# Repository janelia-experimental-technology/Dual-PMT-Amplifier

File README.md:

# Dual-PMT-Amplifier
Dual amplifier for PMTs

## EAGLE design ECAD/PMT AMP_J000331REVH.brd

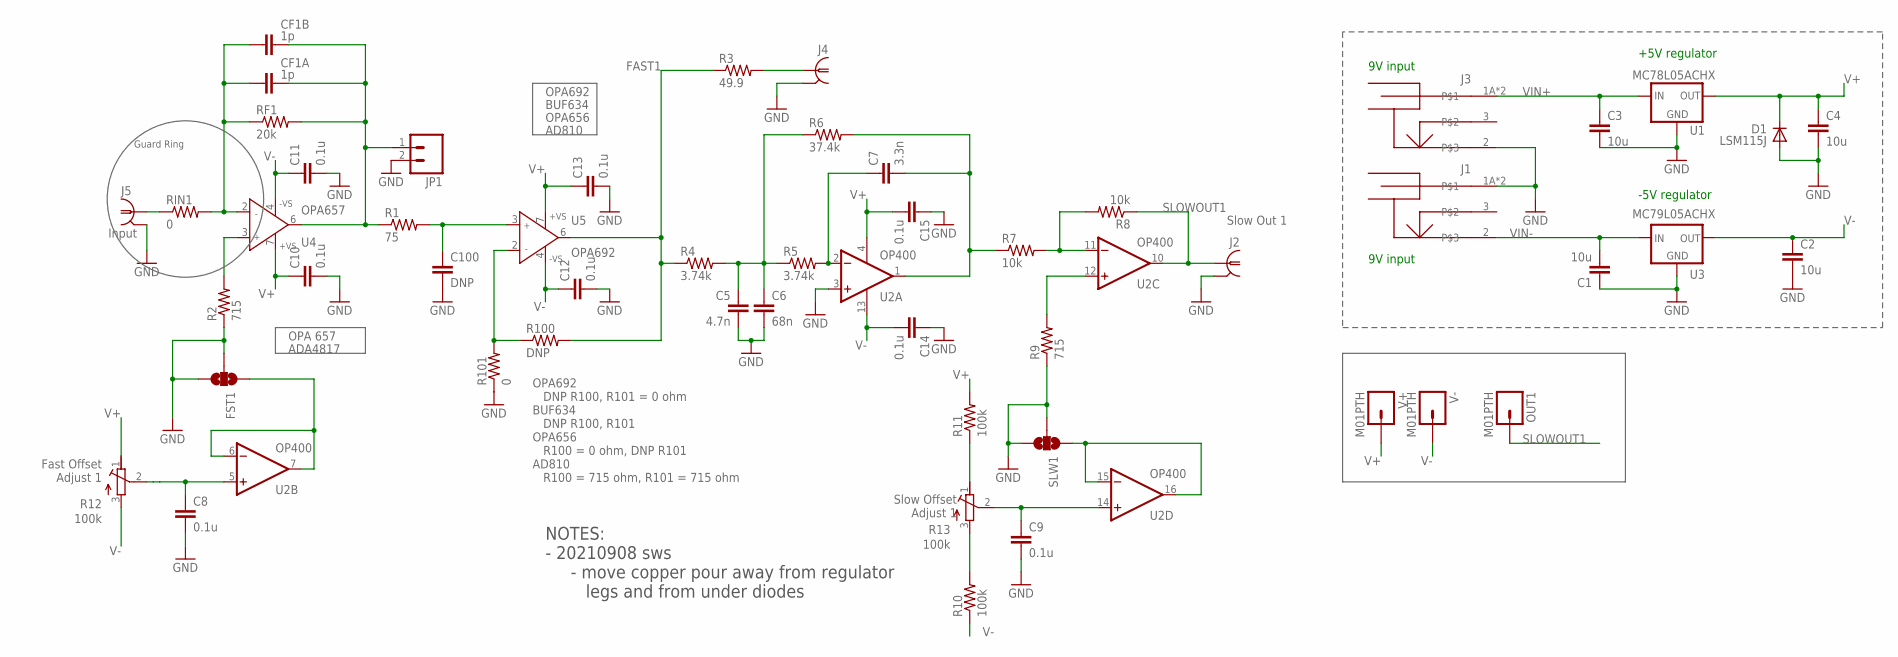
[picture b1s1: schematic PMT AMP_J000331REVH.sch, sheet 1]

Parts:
C1, C2, C3, C4: 10u; C1206
C5: 4.7n; C0805
C6: 68n; C0805
C7: 3.3n; C0805
C8, C9, C10, C11, C12, C13, C14, C15: 0.1u; C0603
C100: DNP; C0805
CF1A, CF1B: 1p; C1206
D1: LSM115J; DO214BA
FST1: SOLDERJUMPER_2WAYS; SJ_3
J1, J3: POWER_JACK_SHUNTPJ-002; PJ-002
J2, J4, J5: 1-227161-0; AMP_227161; MPN 5413879-1
JP1: M02LOCK; 1X02_LOCK
OUT1: M01PTH; 1X01
R1: 75; R0805
R2, R9: 715; R0805
R3: 49.9; 2512LONG
R4, R5: 3.74k; R0805
R6: 37.4k; R0805
R7, R8: 10k; R0805
R10, R11: 100k; R0805
R12, R13: 100k; RTRIM3006P; MPN 3006P-1-104LF
R100: DNP; R0805
R101: 0; R0805
RF1: 20k; R1206
RIN1: 0; R0805
SLW1: SOLDERJUMPER_2WAYS; SJ_3
U1: MC78L05ACHX; SOT89
U2: OP400; SO16L
U3: MC79L05ACHX; SOT89
U4: OPA657; SO8
U5: OPA692; SO8
V+: M01PTH; 1X01
V-: M01PTH; 1X01

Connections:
FAST1: R3.1, R4.1, R100.2, U5.6 (OUT)
FO1: J4.1, R3.2
GND: C1.1, C2.2, C3.2, C4.2, C5.2, C6.2, C8.2, C9.2, C10.2, C11.2, C12.2, C13.2, C14.1, C15.1, C100.2, D1.A, FST1.2, FST1.3, J1.1A, J1.1B, J2.2 (GND), J3.2, J4.2 (GND), J5.2 (GND), JP1.2, R2.1, R9.1, R101.1, SLW1.2, SLW1.3, U1.2 (GND), U1.2@1 (GND), U2.3 (+IN), U3.1 (GND); also elsewhere on the board
unnamed: CF1A.1, CF1B.1, RF1.1, RIN1.2, U4.2 (IN-)
unnamed: R7.2, R8.2, U2.11 (-IN)
unnamed: C100.1, R1.2, U5.3 (IN+)
unnamed: C8.1, R12.2 (S), U2.5 (+IN)
unnamed: C9.1, R13.2 (S), U2.14 (+IN)
unnamed: R11.1, R13.1 (E)
unnamed: R10.2, R13.3 (A)
unnamed: J5.1, RIN1.1
unnamed: R100.1, R101.2, U5.2 (IN-)
unnamed: C7.1, R5.2, U2.2 (-IN)
unnamed: SLW1.1, U2.15 (-IN), U2.16 (OUT)
unnamed: FST1.1, U2.6 (-IN), U2.7 (OUT)
unnamed: C7.2, R6.2, R7.1, U2.1 (OUT)
unnamed: C5.1, C6.1, R4.2, R5.1, R6.1
unnamed: R9.2, U2.12 (+IN)
unnamed: R2.2, U4.3 (IN+)
SLOWOUT1: J2.1, OUT1.1, R8.1, U2.10 (OUT)
U4OUT1: CF1A.2, CF1B.2, JP1.1, R1.1, RF1.2, U4.6 (OUT)
V+: C4.1, C10.1, C13.1, C15.2, D1.C, R11.2, R12.1 (E), U1.1 (OUT), U2.4 (V+), U4.7 (+VS), U5.7 (+VS), V+.1
V-: C2.1, C11.1, C12.1, C14.2, R10.1, R12.3 (A), U2.13 (V-), U3.3 (OUT), U4.4 (-VS), U5.4 (-VS), V-.1
VIN+: C3.1, J3.1A, J3.1B, U1.3 (IN); also elsewhere on the board
VIN-: C1.2, J1.2, U3.2 (IN), U3.2@1 (IN); also elsewhere on the board

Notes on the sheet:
9V input
+5V regulator
-5V regulator
OPA 657
ADA4817
OPA692
OPA656
AD810
Slow Offset Adjust 1
Fast Offset Adjust 1
Slow Out 1
Input
OPA692 DNP R100, R101 = 0 ohm BUF634 DNP R100, R101 OPA656 R100 = 0 ohm, DNP R101 AD810 R100 = 715 ohm, R101 = 715 ohm
Guard Ring
BUF634
NOTES: - 20210908 sws - move copper pour away from regulator legs and from under diodes

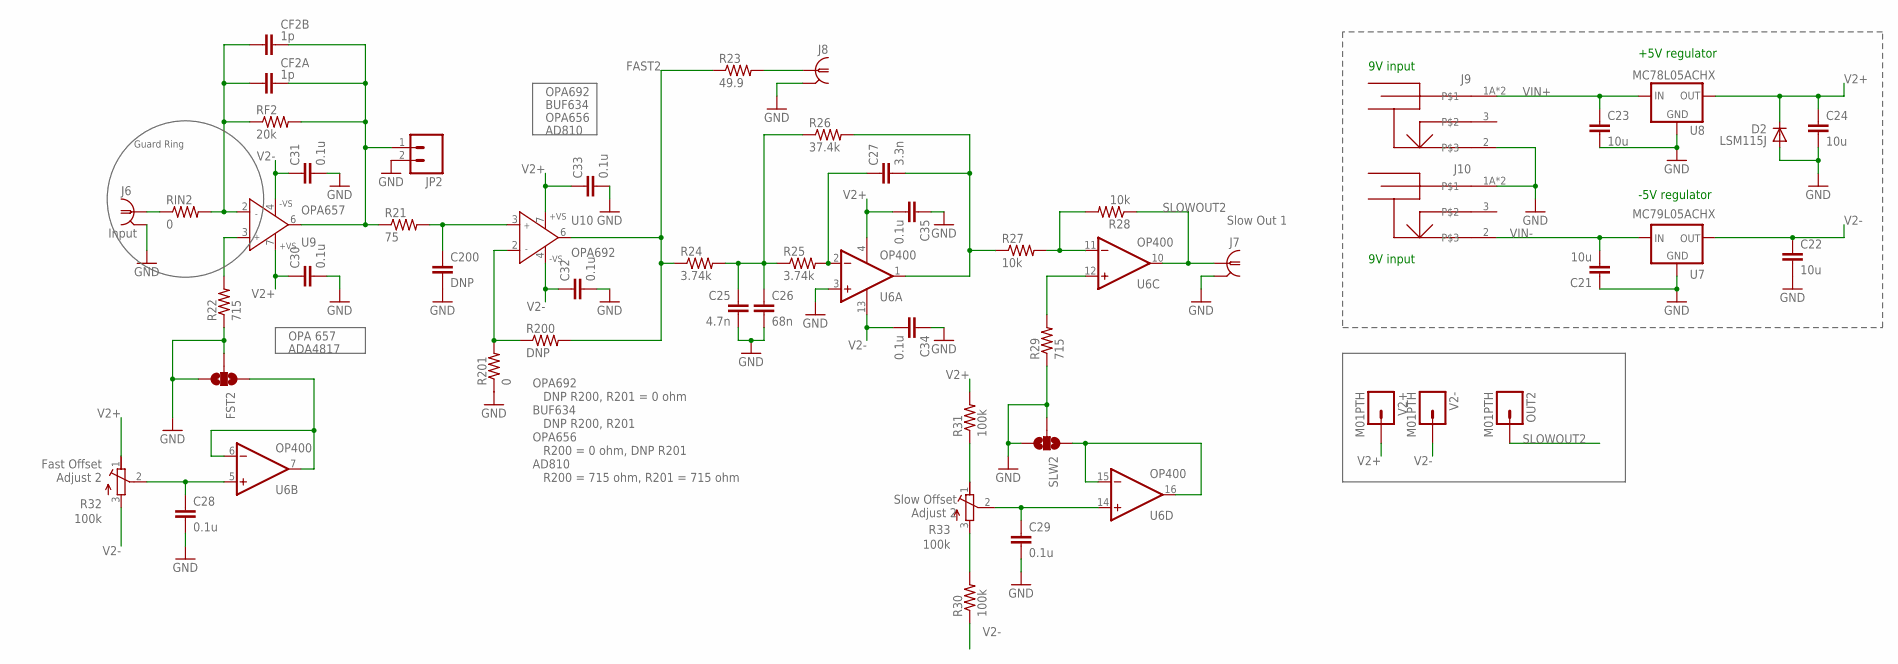
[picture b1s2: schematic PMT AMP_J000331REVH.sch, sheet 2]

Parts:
C21, C22, C23, C24: 10u; C1206
C25: 4.7n; C0805
C26: 68n; C0805
C27: 3.3n; C0805
C28, C29, C30, C31, C32, C33, C34, C35: 0.1u; C0603
C200: DNP; C0805
CF2A, CF2B: 1p; C1206
D2: LSM115J; DO214BA
FST2: SOLDERJUMPER_2WAYS; SJ_3
J6, J7, J8: 1-227161-0; AMP_227161; MPN 5413879-1
J9, J10: POWER_JACK_SHUNTPJ-002; PJ-002
JP2: M02LOCK; 1X02_LOCK
OUT2: M01PTH; 1X01
R21: 75; R0805
R22, R29: 715; R0805
R23: 49.9; 2512LONG
R24, R25: 3.74k; R0805
R26: 37.4k; R0805
R27, R28: 10k; R0805
R30, R31: 100k; R0805
R32, R33: 100k; RTRIM3006P; MPN 3006P-1-104LF
R200: DNP; R0805
R201: 0; R0805
RF2: 20k; R1206
RIN2: 0; R0805
SLW2: SOLDERJUMPER_2WAYS; SJ_3
U6: OP400; SO16L
U7: MC79L05ACHX; SOT89
U8: MC78L05ACHX; SOT89
U9: OPA657; SO8
U10: OPA692; SO8
V2+, V2-: M01PTH; 1X01

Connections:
FAST2: R23.1, R24.1, R200.2, U10.6 (OUT)
FO2: J8.1, R23.2
GND: C21.1, C22.2, C23.2, C24.2, C25.2, C26.2, C28.2, C29.2, C30.2, C31.2, C32.2, C33.2, C34.1, C35.1, C200.2, D2.A, FST2.2, FST2.3, J6.2 (GND), J7.2 (GND), J8.2 (GND), J9.2, J10.1A, J10.1B, JP2.2, R22.1, R29.1, R201.1, SLW2.2, SLW2.3, U6.3 (+IN), U7.1 (GND), U8.2 (GND), U8.2@1 (GND); also elsewhere on the board
unnamed: CF2A.1, CF2B.1, RF2.1, RIN2.2, U9.2 (IN-)
unnamed: J6.1, RIN2.1
unnamed: C200.1, R21.2, U10.3 (IN+)
unnamed: R200.1, R201.2, U10.2 (IN-)
unnamed: C28.1, R32.2 (S), U6.5 (+IN)
unnamed: C27.1, R25.2, U6.2 (-IN)
unnamed: C29.1, R33.2 (S), U6.14 (+IN)
unnamed: C27.2, R26.2, R27.1, U6.1 (OUT)
unnamed: SLW2.1, U6.15 (-IN), U6.16 (OUT)
unnamed: R27.2, R28.2, U6.11 (-IN)
unnamed: R31.1, R33.1 (E)
unnamed: R30.2, R33.3 (A)
unnamed: C25.1, C26.1, R24.2, R25.1, R26.1
unnamed: FST2.1, U6.6 (-IN), U6.7 (OUT)
unnamed: R29.2, U6.12 (+IN)
unnamed: R22.2, U9.3 (IN+)
SLOWOUT2: J7.1, OUT2.1, R28.1, U6.10 (OUT)
U9OUT1: CF2A.2, CF2B.2, JP2.1, R21.1, RF2.2, U9.6 (OUT)
V2+: C24.1, C30.1, C33.1, C35.2, D2.C, R31.2, R32.1 (E), U6.4 (V+), U8.1 (OUT), U9.7 (+VS), U10.7 (+VS), V2+.1
V2-: C22.1, C31.1, C32.1, C34.2, R30.1, R32.3 (A), U6.13 (V-), U7.3 (OUT), U9.4 (-VS), U10.4 (-VS), V2-.1
VIN+: C23.1, J9.1A, J9.1B, U8.3 (IN); also elsewhere on the board
VIN-: C21.2, J10.2, U7.2 (IN), U7.2@1 (IN); also elsewhere on the board

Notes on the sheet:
9V input
+5V regulator
-5V regulator
OPA 657
ADA4817
OPA692
OPA656
AD810
Slow Offset Adjust 2
Fast Offset Adjust 2
Slow Out 1
Input
OPA692 DNP R200, R201 = 0 ohm BUF634 DNP R200, R201 OPA656 R200 = 0 ohm, DNP R201 AD810 R200 = 715 ohm, R201 = 715 ohm
Guard Ring
BUF634

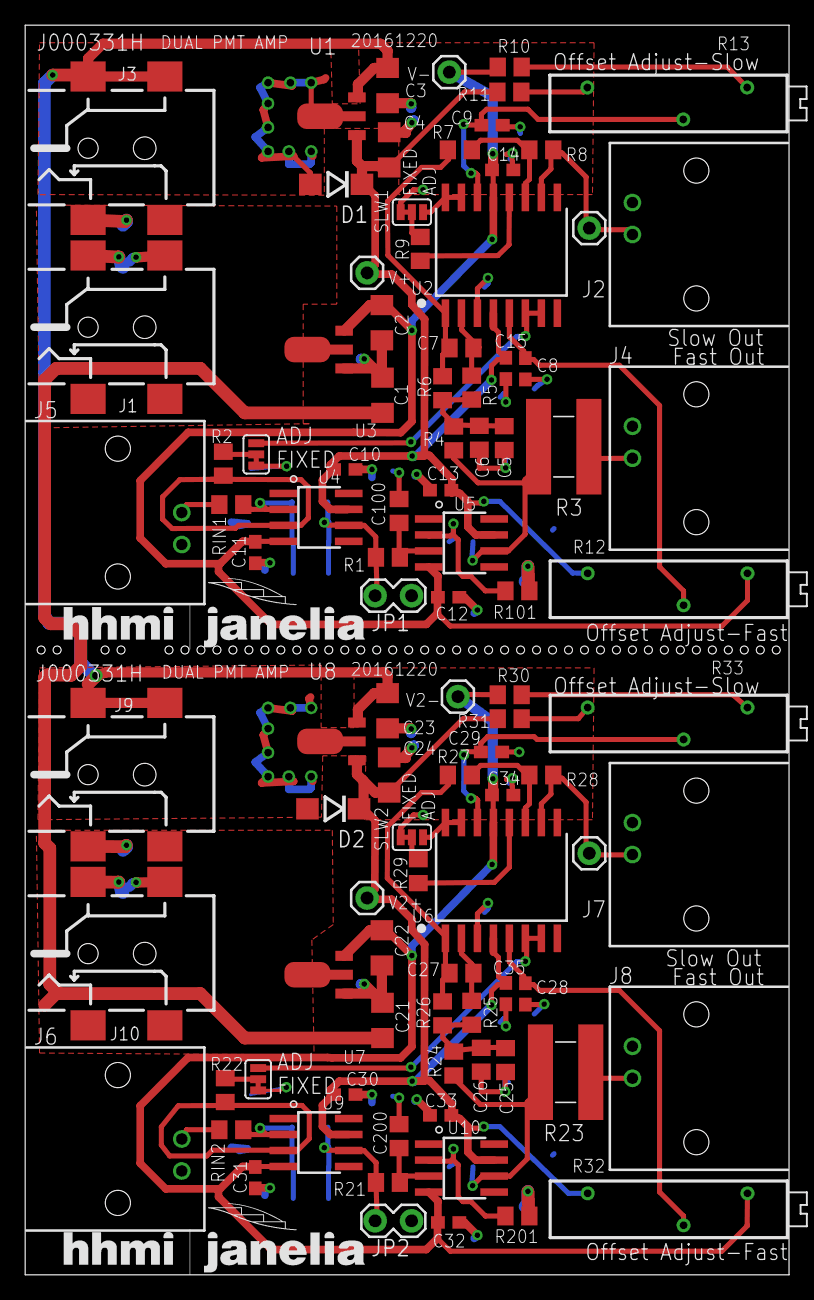
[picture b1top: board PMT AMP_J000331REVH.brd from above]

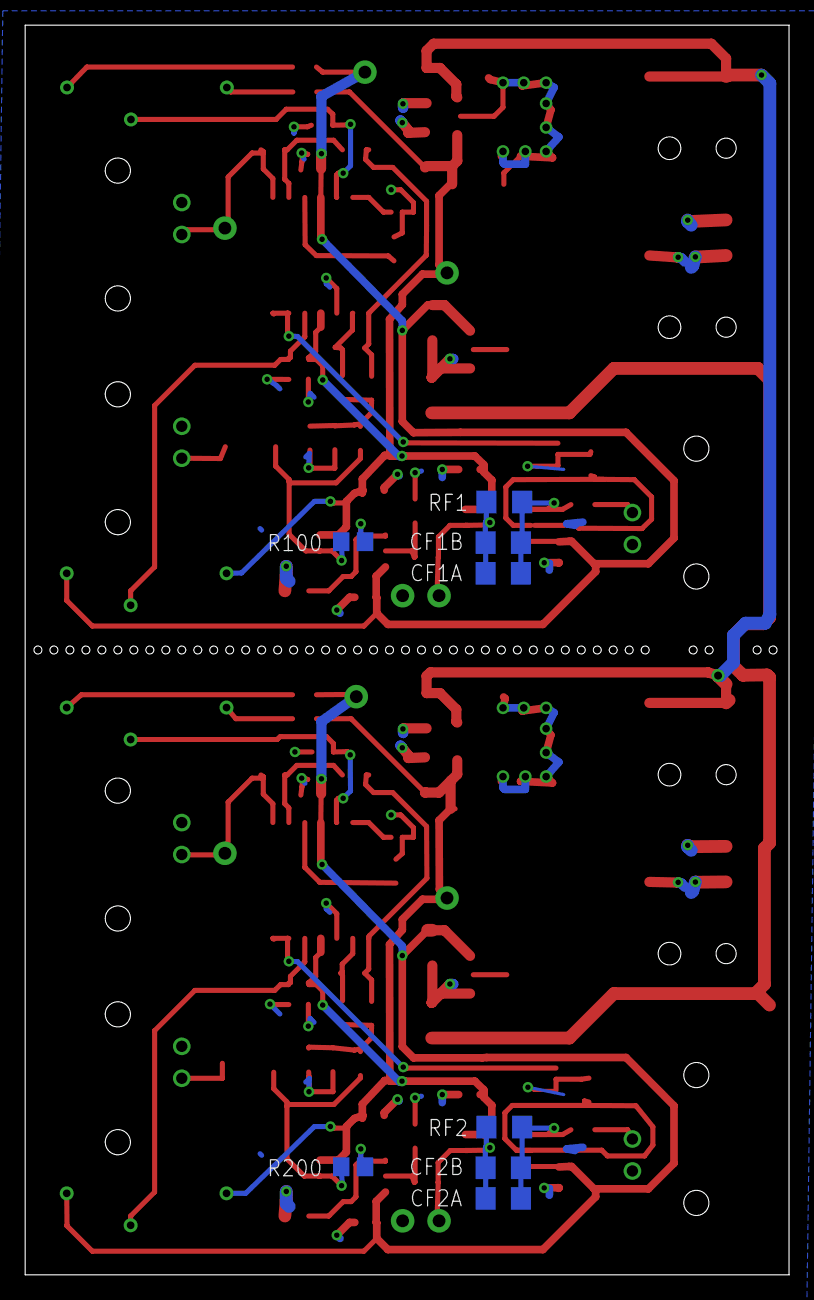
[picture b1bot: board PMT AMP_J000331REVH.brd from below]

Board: 2 copper layers, 60.7 x 99.3 mm, 106 parts (8 on the bottom side), 47 nets.

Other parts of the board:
U$1, U$2: JFRC-LOGOLOGO_JANELIA_2014; LOGO_JANELIA_2014

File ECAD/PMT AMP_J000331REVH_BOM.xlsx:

Qty | Value | Device | Package | Parts | Description | MANUFACTURER | MANUFACTURER PN | DIGIKEY PART NUMBER
6 | DNP | M01PTH | 1X01 | OUT1, OUT2, V+, V-, V2+, V2- | Header 1 | - | - | -
2 | 1x02 | M02LOCK | 1X02_LOCK | JP1, JP2 | Header 2 | Wurth | 61300211121 | 732-5315-ND
2 | 49.9 | RESISTOR-POWER2512WIDE | 2512LONG | R3, R23 | RES SMD 49.9 OHM 2W 2512 WIDE | Vishay Dale | RCL122549R9FKEG | RCL49.9ECT-ND
6 | 227161 | 5227161-9 | AMP_227161 | J2, J4, J5, J6, J7, J8 | JACK, RIGHT ANGLE, 50 OHM, PCB, BNC | TE Connectivity | 5227161-9 | A32261-ND
6 |  | 1-1634816-0 | AMP_227161 | J2, J4, J5, J6, J7, J8 | CONN NUT FOR BNC AND TNC CONN | TE Connectivity | 1-1634816-0 | A97566-ND
6 |  | 1-1634817-0 | AMP_227161 | J2, J4, J5, J6, J7, J8 | CONN LOCKWSH FOR BNC & TNC CONN | TE Connectivity | 1-1634817-0 | A97567-ND
16 | 0.1u | C-EUC0603 | C0603 | C8, C9, C10, C11, C12, C13, C14, C15, C28, C29, C30, C31, C32, C33, C34, C35 | CAPACITOR, European symbol | Vishay Vitramon | VJ0603Y104JXXAC | 720-1545-1-ND
2 | 3.3n | C-EUC0805 | C0805 | C7, C27 | CAPACITOR, European symbol | KEMET | C0805C332F3GACTU | 399-8066-1-ND
2 | 4.7n | C-EUC0805 | C0805 | C5, C25 | CAPACITOR, European symbol | KEMET | C0805C472GAGAC7800 | 399-13494-1-ND
2 | 68n | C-EUC0805 | C0805 | C6, C26 | CAPACITOR, European symbol | KEMET | C0805C683J5RAC7800 | 399-14629-1-ND
2 | DNP | C-EUC0805 | C0805 | C100, C200 | CAPACITOR, European symbol | - | - | -
8 | 10u | C-EUC1206 | C1206 | C1, C2, C3, C4, C21, C22, C23, C24 | CAPACITOR, European symbol | KEMET | C1206C106J3RACAUTO | 399-15734-1-ND
4 | 1p | C-EUC1206 | C1206 | CF1A, CF1B, CF2A, CF2B | CAPACITOR, European symbol | KEMET | C1206C109C5GACTU | 399-1178-1-ND
2 | LSM115J | DIODE-DO214BA | DO214BA | D1, D2 | DIODE | Microsemi | LSM115JE3/TR13 | LSM115JE3/TR13CT-ND
4 | PJ-002BH | POWER_JACK_SHUNTPJ-002 | PJ-002 | J1, J3, J9, J10 | CONN PWR JACK 2.5X5.5MM SOLDER | CUI | PJ-002BH-SMT-TR | CP-002BHPJTR-ND
4 | 0 | R-US_R0805 | R0805 | R100, R200, RIN1, RIN2 | RESISTOR, American symbol | Vishay Dale | CRCW08050000Z0EA | 541-0.0ACT-ND
4 | 100k | R-US_R0805 | R0805 | R10, R11, R30, R31 | RESISTOR, American symbol | Vishay Dale | TNPW0805100KBEEA | TNP100KABCT-ND
4 | 10k | R-US_R0805 | R0805 | R7, R8, R27, R28 | RESISTOR, American symbol | Vishay Dale | TNPW080510K0BEEA | TNP10.0KABCT-ND
4 | 3.74k | R-US_R0805 | R0805 | R4, R5, R24, R25 | RESISTOR, American symbol | Vishay Dale | TNPW08053K74BEEA | 541-3791-1-ND
2 | 37.4k | R-US_R0805 | R0805 | R6, R26 | RESISTOR, American symbol | Vishay Dale | TNPW080537K4BEEA | 541-3779-1-ND
4 | 715 | R-US_R0805 | R0805 | R2, R9, R22, R29 | RESISTOR, American symbol | Vishay Dale | CRCW0805715RFKEA | 541-715CCT-ND
2 | 75 | R-US_R0805 | R0805 | R1, R21 | RESISTOR, American symbol | Vishay Dale | CRCW080575R0JNEA | 541-75ACT-ND
2 | DNP | R-US_R0805 | R0805 | R101, R201 | RESISTOR, American symbol | - | - | -
2 | 20k | R-US_R1206 | R1206 | RF1, RF2 | RESISTOR, American symbol | Vishay Dale | TNPW120620K0BEEA | TNP20.0KACCT-ND
2 | 100k | R-US_R1206 | R1206 | RF1, RF2 | RESISTOR, American symbol | Vishay Dale | TNPW1206100KBEEA | TNP100KACCT-ND
4 | 100k | R-TRIMM3006P | RTRIM3006P | R12, R13, R32, R33 | Trimm resistor | BOURNS | 3006P-1-104LF | 3006P-104LF-ND
4 |  | SOLDERJUMPER_2WAYS | SJ_3 | FST1, FST2, SLW1, SLW2 | Solder Jumper | - | - | -
2 | OP400G | OP400SO16_W | SO16L | U2, U6 | OP AMP | Analog Devices | OP400GSZ | OP400GSZ-ND
2 | OPA692 | AD820R | SO8 | U5, U10 | Single-Supply, Rail-to-Rail, Low Power, FET Input Op Amp | Texas Instruments | OPA692ID | OPA692ID-ND
2 | OPA657 | AD820R | SO8 | U4, U9 | Single-Supply, Rail-to-Rail, Low Power, FET Input Op Amp | Texas Instruments | OPA657UB | OPA657UB-ND
2 | MC78L05ACHX | 78LXXSOT89 | SOT89 | U1, U8 | VOLTAGE REGULATOR | ON Semiconductor | MC78L05ACHX | MC78L05ACHXCT-ND
2 | MC79L05ACHX | 79LXXSOT89 | SOT89 | U3, U7 | VOLTAGE REGULATOR | ON Semiconductor | MC79L05ACHX | MC79L05ACHXCT-ND
2 |  | PowerSupply |  |  | 5.4 Watt AC/DC Unregulated Linear Wall Adapter | Jameco | 100175

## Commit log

2025-08-05 fix up
